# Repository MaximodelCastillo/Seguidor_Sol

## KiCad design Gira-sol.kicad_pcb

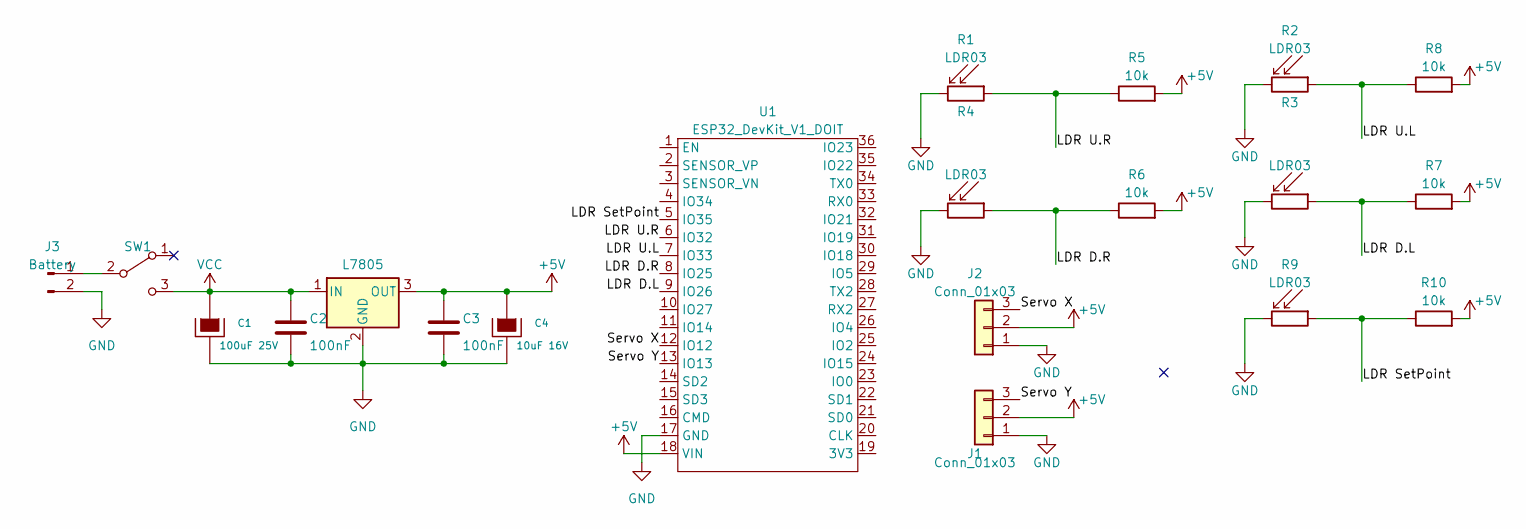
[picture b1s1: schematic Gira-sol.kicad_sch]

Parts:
C1: 100uF 25V; CAP_ELEC_5x11mm
C2, C3: 100nF; CAP_0.1
C4: 10uF 16V; CAP_ELEC_5x11mm
J1, J2: Conn_01x03; Pin_Header_3
J3: Battery; BORNERA2
R1, R2, R3, R4: LDR03; R_LDR_4.9x4.2mm_P2.54mm_Vertical
R5, R6, R7, R8, R10: 10k; RES0.3
R9: LDR03; R_LDR_5.0x4.1mm_P3mm_Vertical
SW1: SW_SPDT; SW_SPDT_TH_Vertical
U1: ESP32_DevKit_V1_DOIT; ESP32_DEVKIT_V1_DOIT
U2: L7805; TO-220

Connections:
+5V: C3.1, C4.1, J1.2, J2.2, R5.2, R6.2, R7.2, R8.2, R10.2, U1.18 (VIN), U2.3 (OUT)
/LDR D.L: R3.1, R7.1, U1.9 (IO26)
/LDR D.R: R4.1, R6.1, U1.8 (IO25)
/LDR SetPoint: R9.1, R10.1, U1.5 (IO35)
/LDR U.L: R2.1, R8.1, U1.7 (IO33)
/LDR U.R: R1.1, R5.1, U1.6 (IO32)
/Servo X: J2.3, U1.12 (IO12)
/Servo Y: J1.3, U1.13 (IO13)
GND: C1.2, C2.2, C3.2, C4.2, J1.1, J2.1, J3.2, R1.2, R2.2, R3.2, R4.2, R9.2, U1.17 (GND), U2.2 (GND)
unnamed: J3.1, SW1.2 (B)
VCC: C1.1, C2.1, SW1.3 (C), U2.1 (IN)

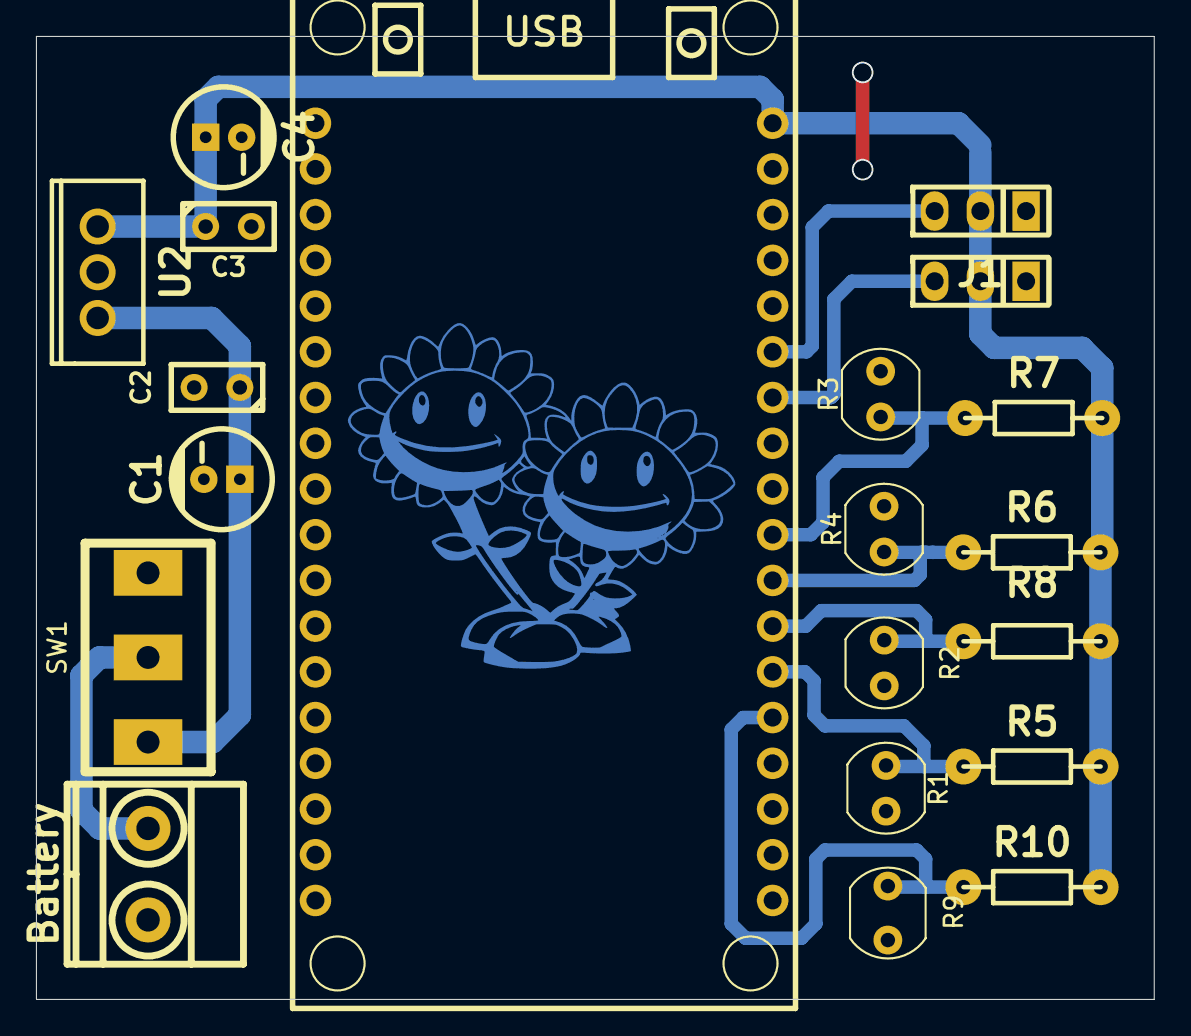
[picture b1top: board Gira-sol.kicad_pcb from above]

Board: 2 copper layers, 62.1 x 53.5 mm, 20 parts (0 on the bottom side), 11 nets.

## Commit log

2023-12-13 proyecto v1
